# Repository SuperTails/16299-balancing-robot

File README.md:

# 16299 Balancing Robot PCB

Updated version of the PCB for 16299.

A submodule is used for some parts, so be sure to clone recursively:
```bash
git clone --recursive https://github.com/SuperTails/16299-balancing-robot.git
```

## Ordering PCBs

### 1 - Generate Bill of Materials

To generate the BoM:

1. Open the schematic editor
2. Open the "edit symbol fields" menu (table icon along the top ribbon)
3. Ensure the settings are as shown below
4. Hit "export".

### 2 - Generate Gerber Files

To generate the gerber files:
1. Open the PCB editor
2. File > Fabrication Outputs > Gerbers (.gbr)...
3. Ensure the settings are as shown below, including...
4. ... Make sure you set your output folder to `fab/`.
5. Click "Plot"

More information for plotting Gerber and Drill files is available on
[JLC's guide](https://jlcpcb.com/help/article/how-to-generate-gerber-and-drill-files-in-kicad-7).

### 3 - Generate Drill Files

To generate the drill files:
1. From the Gerbers menu in the previous step, click "Generate Drill Files"
3. Ensure the settings are as shown below
5. Click "Generate"

More information for plotting Gerber and Drill files is available on
[JLC's guide](https://jlcpcb.com/help/article/how-to-generate-gerber-and-drill-files-in-kicad-7).

### 4 - Generate Placement Files

To generate the placement files:
1. Open the PCB editor
2. File > Fabrication Outputs > Component Placement (.pos, .gbr)...
3. Ensure the settings are as shown below
4. Click "Generate Position File"

### 5 - File Format Conversion

To convert the files into JLC's preferred format, run the `format_bom.py` script:

```bash
python3 format_bom.py
```

This will generate `fab/bom-jlc.csv` and `fab/balancingrobot-top-pos-jlc.csv`,
which should be used for JLC's PCB assembly options (discussed later).

### 6 - Upload Gerbers

Zip the `fab/` directory and upload it to [JLC's website](https://jlcpcb.com/).
Rarely, the file upload can take up to 10 minutes to complete.

### 7 - Select Ordering Options

Most settings should default correctly,
but there are a few changes:

1. Set the quantity to the desired amount
2. Ensure that the order mark is set to "Order Number (Specify Position)"
3. Enable "PCB Assembly"
4. Hit "next"

### 8 - Uploading BOM and Placing Components

When prompted to "Upload BOM" and "Add CPL file",
upload `fab/bom-jlc.csv` and `fab/balancingrobot-top-pos-jlc.csv`.

It may issue a warning that D9 and D10 are not present in the CPL,
this is normal and you can continue.
D9 and D10 are the IR LEDs which are mounted on the underside of the board,
and doing assembly for both top and bottom components makes shipping difficult.

All parts should be selected in the right column and there should be no other errors.

When moving on to placement, JLC may note that
"The system detects component that may be offset from the PCB,
does it try to automatically align it?"
Click **cancel** on this prompt, as it will displace many of the components to the wrong place.

The through-hole components typically need to be both rotated and dragged to fit;
the surface mount components should **only be rotated**.

Ensure that all surface mount components
**have the pink dot (pin 1) aligned with the corresponding silkscreen arrow**.
Some of the SMD components may be upside-down.

There will be four rows of header pins far above the rest of the PCB (shown below);
these are the sockets for the Arduino Nano and the motor driver.
Be sure to place them as well.

Once placement is finished, the board should appear as shown below:

When prompted to select a category for your order, I usually select "Robot",
as shown below:

This completes all the placement steps,
simply complete the rest of the checkout steps to order the PCB.

**After ordering, you may receive an email saying that the footprint of the 7-segment display is incorrect.**
**As long as the decimal point is on the bottom and the pink dot is in the bottom left, reply to the email and say the placement is correct.**

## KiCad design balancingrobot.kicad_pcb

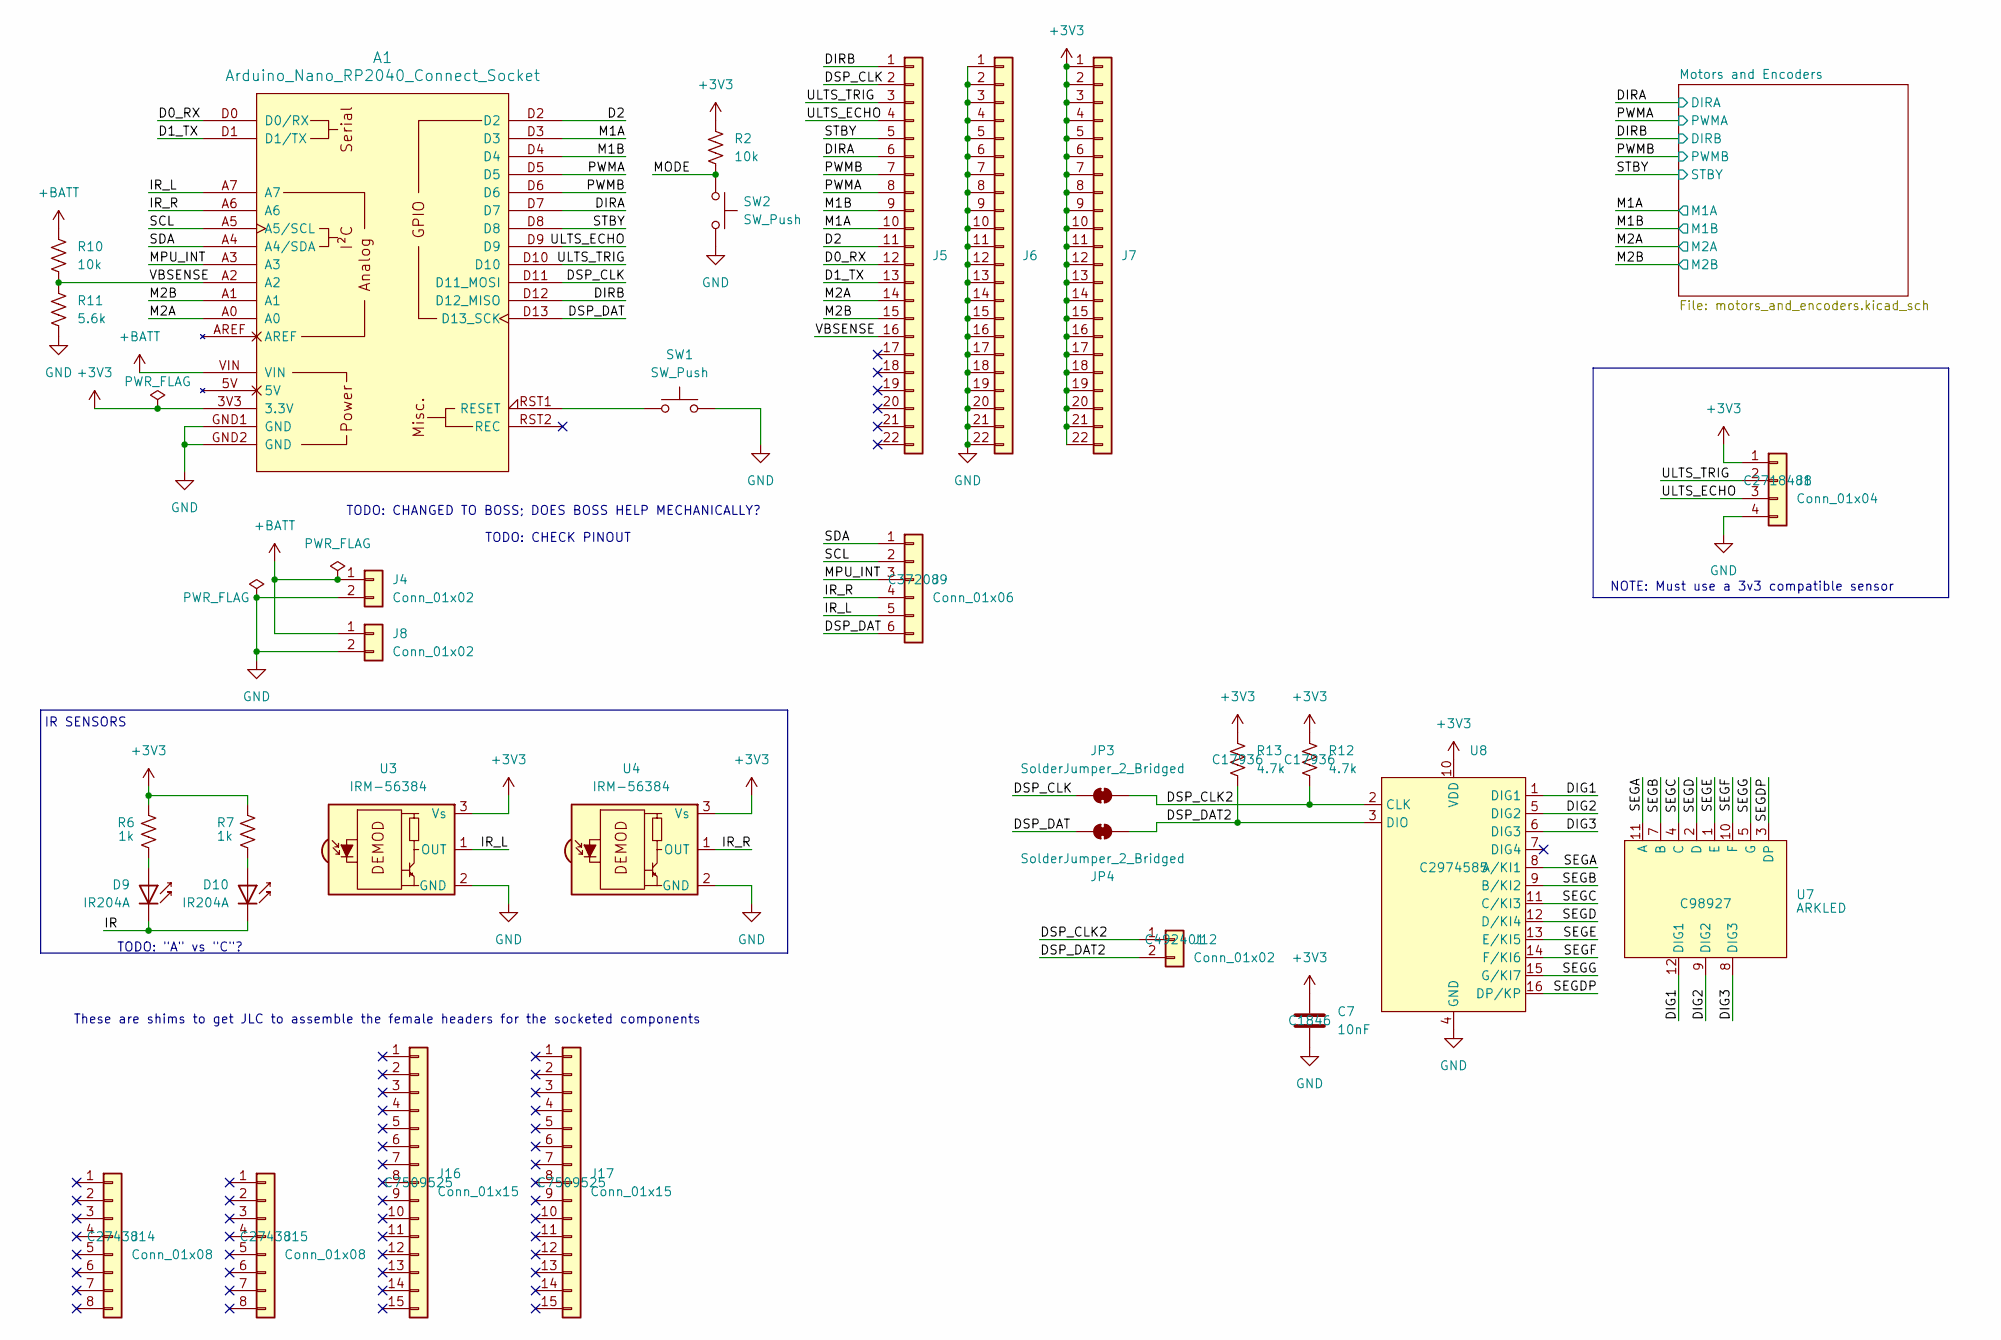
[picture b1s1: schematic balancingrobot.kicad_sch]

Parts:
A1: Arduino_Nano_RP2040_Connect_Socket; Arduino_Nano_Every_Socket
C7: 10nF; C_1206_3216Metric; JLC P/N C1846
D9, D10: IR204A; LED_D3.0mm_IRBlack; JLC P/N C2936547
J1: Conn_01x04; PinSocket_1x04_P2.54mm_Vertical; JLC P/N C2718488
J4: Conn_01x02; JST_XH_S2B-XH-A-1_1x02_P2.50mm_Horizontal; JLC P/N C163035
J5, J6, J7: Conn_01x22; PinHeader_1x22_P2.54mm_Vertical; JLC P/N C725954
J8, J12: Conn_01x02; PinHeader_1x02_P2.54mm_Vertical; JLC P/N C492401
J9: Conn_01x06; PinHeader_1x06_P2.54mm_Vertical; JLC P/N C37208
J14, J15: Conn_01x08; PinSocket_1x08_P2.54mm_Vertical; JLC P/N C27438
J16, J17: Conn_01x15; PinSocket_1x15_P2.54mm_Vertical; JLC P/N C7509525
JP3, JP4: SolderJumper_2_Bridged; SolderJumper-2_P1.3mm_Bridged_RoundedPad1.0x1.5mm
R2, R10: 10k; R_1206_3216Metric; JLC P/N C17902
R6, R7: 1k; R_1206_3216Metric; JLC P/N C4410
R11: 5.6k; R_1206_3216Metric; JLC P/N C18028
R12, R13: 4.7k; R_1206_3216Metric; JLC P/N C17936
SW1, SW2: SW_Push; SW_PUSH_6mm; JLC P/N C255811
U3, U4: IRM-56384; Vishay_MOLD-3Pin; JLC P/N C72048
U7: ARKLED; ARKLED(Wuxi ARK Tech Elec) SP420361N; JLC P/N C98927
U8: SOP-16_3.9x9.9mm_P1.27mm; JLC P/N C2974585

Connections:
+3V3: A1.3V3 (3.3V), C7.1, J1.1, J7.1, J7.2, J7.3, J7.4, J7.5, J7.6, J7.7, J7.8, J7.9, J7.10, J7.11, J7.12, J7.13, J7.14, J7.15, J7.16, J7.17, J7.18, J7.19, J7.20, J7.21, J7.22, R2.1, R6.2, R7.1, R12.1, R13.1, U3.3 (Vs), U4.3 (Vs), U8.10 (VDD); also elsewhere on the board
+BATT: A1.VIN, J4.1, J8.1, R10.1; also elsewhere on the board
/D0_RX: A1.D0 (D0/RX), J5.12
/D1_TX: A1.D1 (D1/TX), J5.13
/D2: A1.D2, J5.11
/DIG1: U7.12 (DIG1), U8.1 (DIG1)
/DIG2: U7.9 (DIG2), U8.5 (DIG2)
/DIG3: U7.8 (DIG3), U8.6 (DIG3)
/DIRA: A1.D7, J5.6; also elsewhere on the board
/DIRB: A1.D12 (D12_MISO), J5.1; also elsewhere on the board
/DSP_CLK: A1.D11 (D11_MOSI), J5.2, JP3.1 (A)
/DSP_CLK2: J12.1, JP3.2 (B), R12.2, U8.2 (CLK)
/DSP_DAT: A1.D13 (D13_SCK), J9.6, JP4.1 (A)
/DSP_DAT2: J12.2, JP4.2 (B), R13.2, U8.3 (DIO)
/IR: D9.1 (K), D10.1 (K)
/IR_L: A1.A7, J9.5, U3.1 (OUT)
/IR_R: A1.A6, J9.4, U4.1 (OUT)
/M1A: A1.D3, J5.10; also elsewhere on the board
/M1B: A1.D4, J5.9; also elsewhere on the board
/M2A: A1.A0, J5.14; also elsewhere on the board
/M2B: A1.A1, J5.15; also elsewhere on the board
/MODE: R2.2, SW2.1
/MPU_INT: A1.A3, J9.3
/PWMA: A1.D5, J5.8; also elsewhere on the board
/PWMB: A1.D6, J5.7; also elsewhere on the board
/SCL: A1.A5 (A5/SCL), J9.2
/SDA: A1.A4 (A4/SDA), J9.1
/SEGA: U7.11 (A), U8.8 (A/KI1)
/SEGB: U7.7 (B), U8.9 (B/KI2)
/SEGC: U7.4 (C), U8.11 (C/KI3)
/SEGD: U7.2 (D), U8.12 (D/KI4)
/SEGDP: U7.3 (DP), U8.16 (DP/KP)
/SEGE: U7.1 (E), U8.13 (E/KI5)
/SEGF: U7.10 (F), U8.14 (F/KI6)
/SEGG: U7.5 (G), U8.15 (G/KI7)
/STBY: A1.D8, J5.5; also elsewhere on the board
/ULTS_ECHO: A1.D9, J1.3, J5.4
/ULTS_TRIG: A1.D10, J1.2, J5.3
/VBSENSE: A1.A2, J5.16, R10.2, R11.1
GND: A1.GND1 (GND), A1.GND2 (GND), C7.2, J1.4, J4.2, J6.1, J6.2, J6.3, J6.4, J6.5, J6.6, J6.7, J6.8, J6.9, J6.10, J6.11, J6.12, J6.13, J6.14, J6.15, J6.16, J6.17, J6.18, J6.19, J6.20, J6.21, J6.22, J8.2, R11.2, SW1.2, SW2.2, U3.2 (GND), U4.2 (GND), U8.4 (GND); also elsewhere on the board
unnamed: A1.RST1 (RESET), SW1.1
unnamed: D9.2 (A), R6.1
unnamed: D10.2 (A), R7.2

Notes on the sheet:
IR SENSORS
TODO: "A" vs "C"?
These are shims to get JLC to assemble the female headers for the socketed components
NOTE: Must use a 3v3 compatible sensor
TODO: CHECK PINOUT
TODO: CHANGED TO BOSS; DOES BOSS HELP MECHANICALLY?

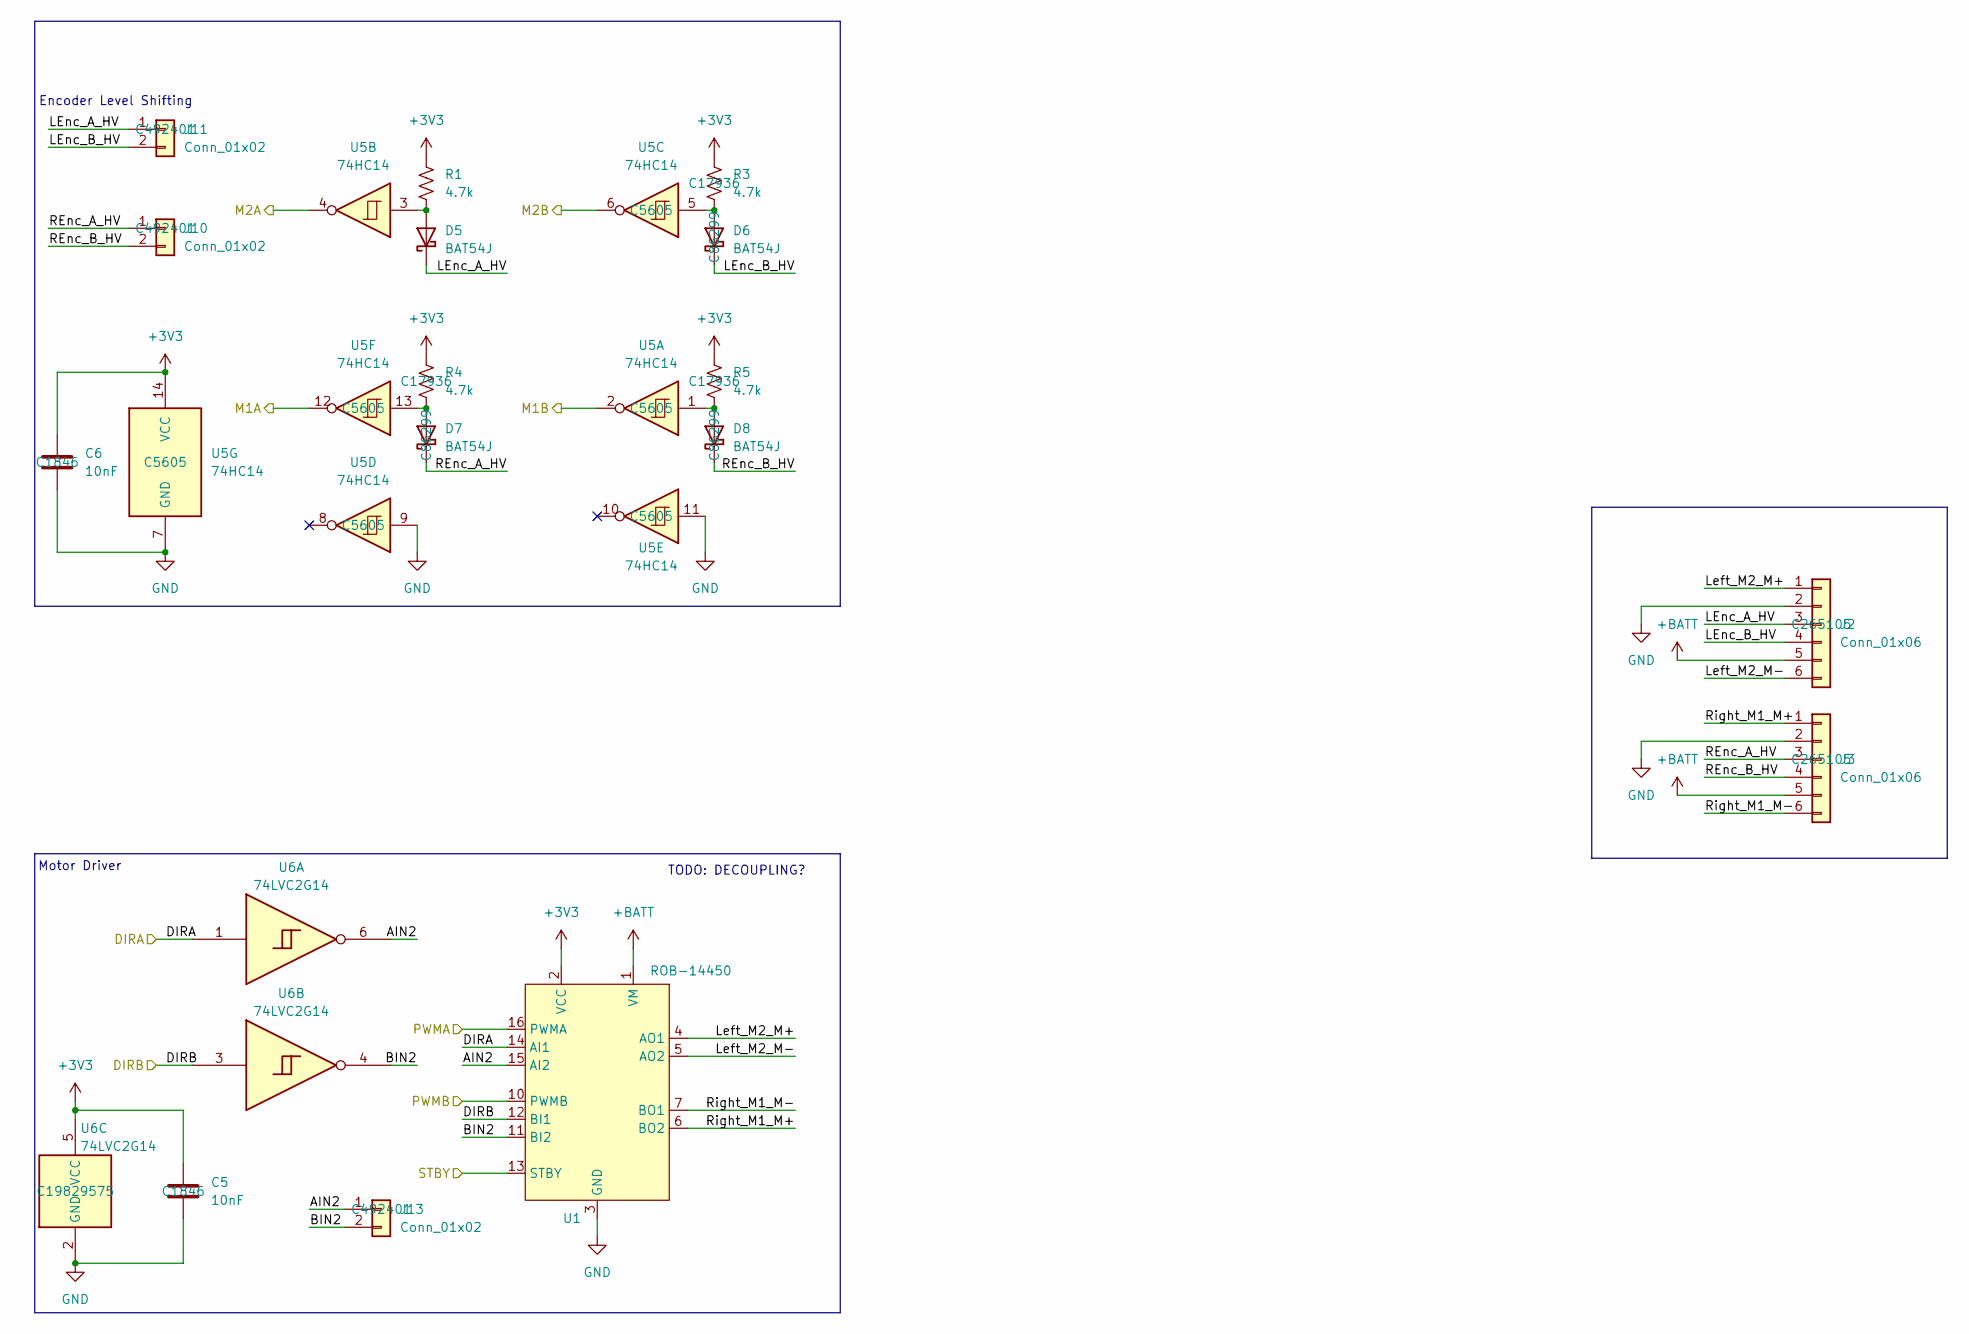
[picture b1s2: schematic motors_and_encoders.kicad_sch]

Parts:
C5, C6: 10nF; C_1206_3216Metric; JLC P/N C1846
D5, D6, D7, D8: BAT54J; D_SOD-323F; JLC P/N C86299
J2, J3: Conn_01x06; JST_PH_S6B-PH-K_1x06_P2.00mm_Horizontal; JLC P/N C265105
J10, J11, J13: Conn_01x02; PinHeader_1x02_P2.54mm_Vertical; JLC P/N C492401
R1, R3, R4, R5: 4.7k; R_1206_3216Metric; JLC P/N C17936
U1: ROB-14450; ROB-14451
U5: 74HC14; SOIC-14_3.9x8.7mm_P1.27mm; JLC P/N C5605
U6: 74LVC2G14; SOT-363_SC-70-6; JLC P/N C19829575

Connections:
+3V3: C5.1, C6.1, R1.2, R3.2, R4.2, R5.2, U1.2 (VCC), U5.14 (VCC), U6.5 (VCC); also elsewhere on the board
+BATT: J2.5, J3.5, U1.1 (VM); also elsewhere on the board
/DIRA: U1.14 (AI1), U6.1; also elsewhere on the board
/DIRB: U1.12 (BI1), U6.3; also elsewhere on the board
/M1A: U5.12; also elsewhere on the board
/M1B: U5.2; also elsewhere on the board
/M2A: U5.4; also elsewhere on the board
/M2B: U5.6; also elsewhere on the board
/Motors and Encoders/AIN2: J13.1, U1.15 (AI2), U6.6
/Motors and Encoders/BIN2: J13.2, U1.11 (BI2), U6.4
/Motors and Encoders/LEnc_A_HV: D5.1 (K), J2.3, J11.1
/Motors and Encoders/LEnc_B_HV: D6.1 (K), J2.4, J11.2
/Motors and Encoders/Left_M2_M+: J2.1, U1.4 (AO1)
/Motors and Encoders/Left_M2_M-: J2.6, U1.5 (AO2)
/Motors and Encoders/REnc_A_HV: D7.1 (K), J3.3, J10.1
/Motors and Encoders/REnc_B_HV: D8.1 (K), J3.4, J10.2
/Motors and Encoders/Right_M1_M+: J3.1, U1.6 (BO2)
/Motors and Encoders/Right_M1_M-: J3.6, U1.7 (BO1)
/PWMA: U1.16 (PWMA); also elsewhere on the board
/PWMB: U1.10 (PWMB); also elsewhere on the board
/STBY: U1.13 (STBY); also elsewhere on the board
GND: C5.2, C6.2, J2.2, J3.2, U1.3 (GND), U1.8 (GND), U1.9 (GND), U5.7 (GND), U5.9, U5.11, U6.2 (GND); also elsewhere on the board
unnamed: D5.2 (A), R1.1, U5.3
unnamed: D6.2 (A), R3.1, U5.5
unnamed: D7.2 (A), R4.1, U5.13
unnamed: D8.2 (A), R5.1, U5.1

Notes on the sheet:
Encoder Level Shifting
TODO: DECOUPLING?
Motor Driver

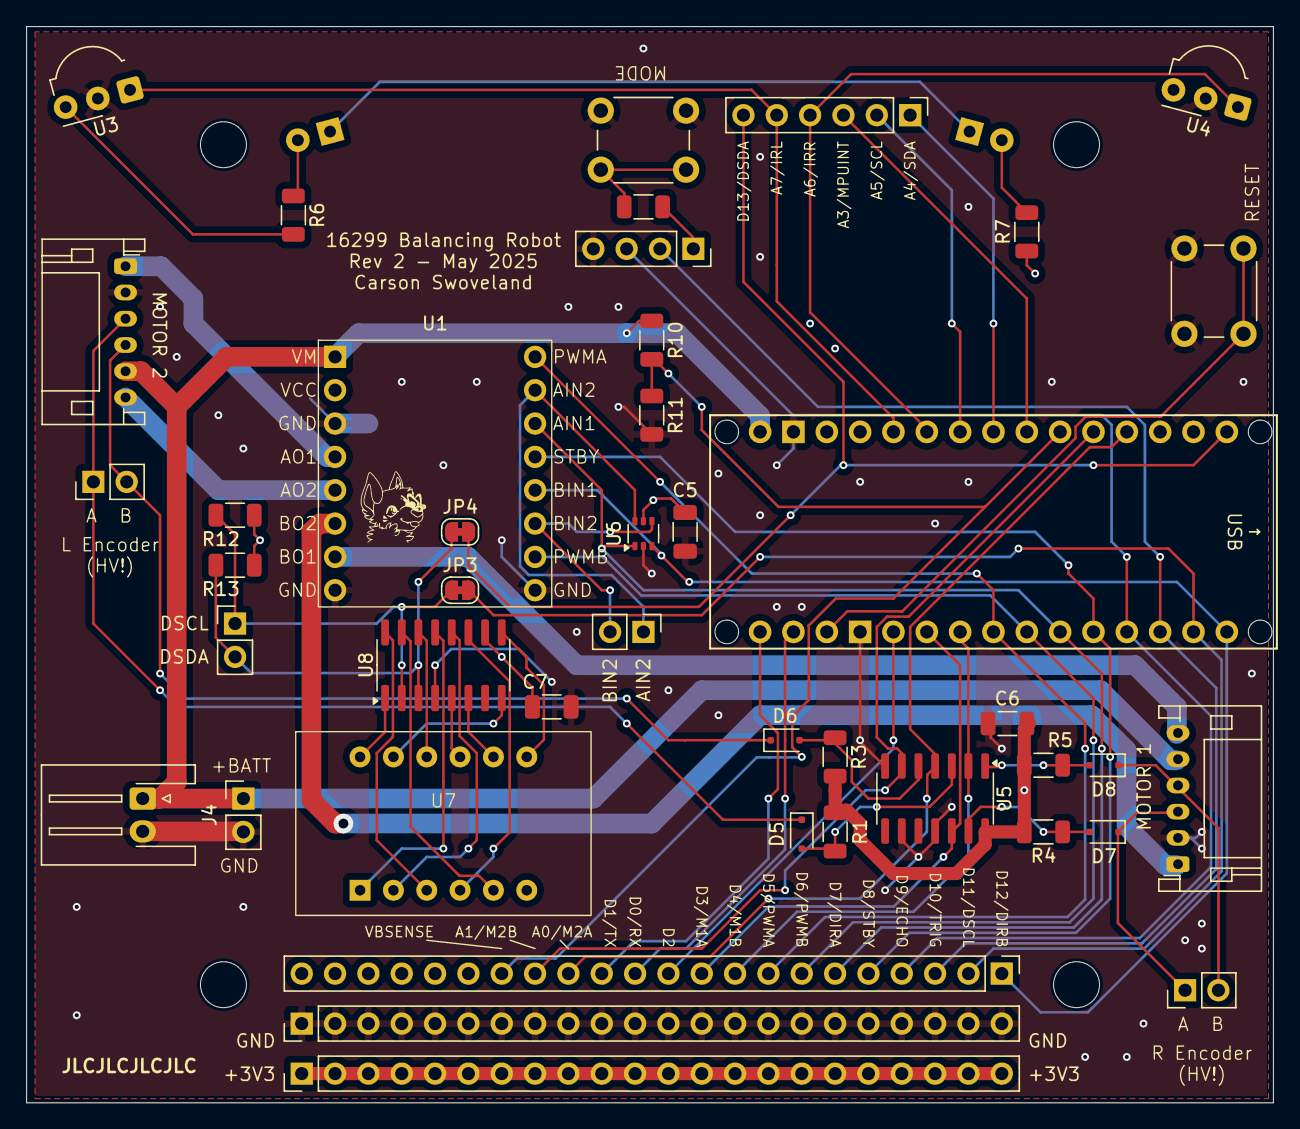
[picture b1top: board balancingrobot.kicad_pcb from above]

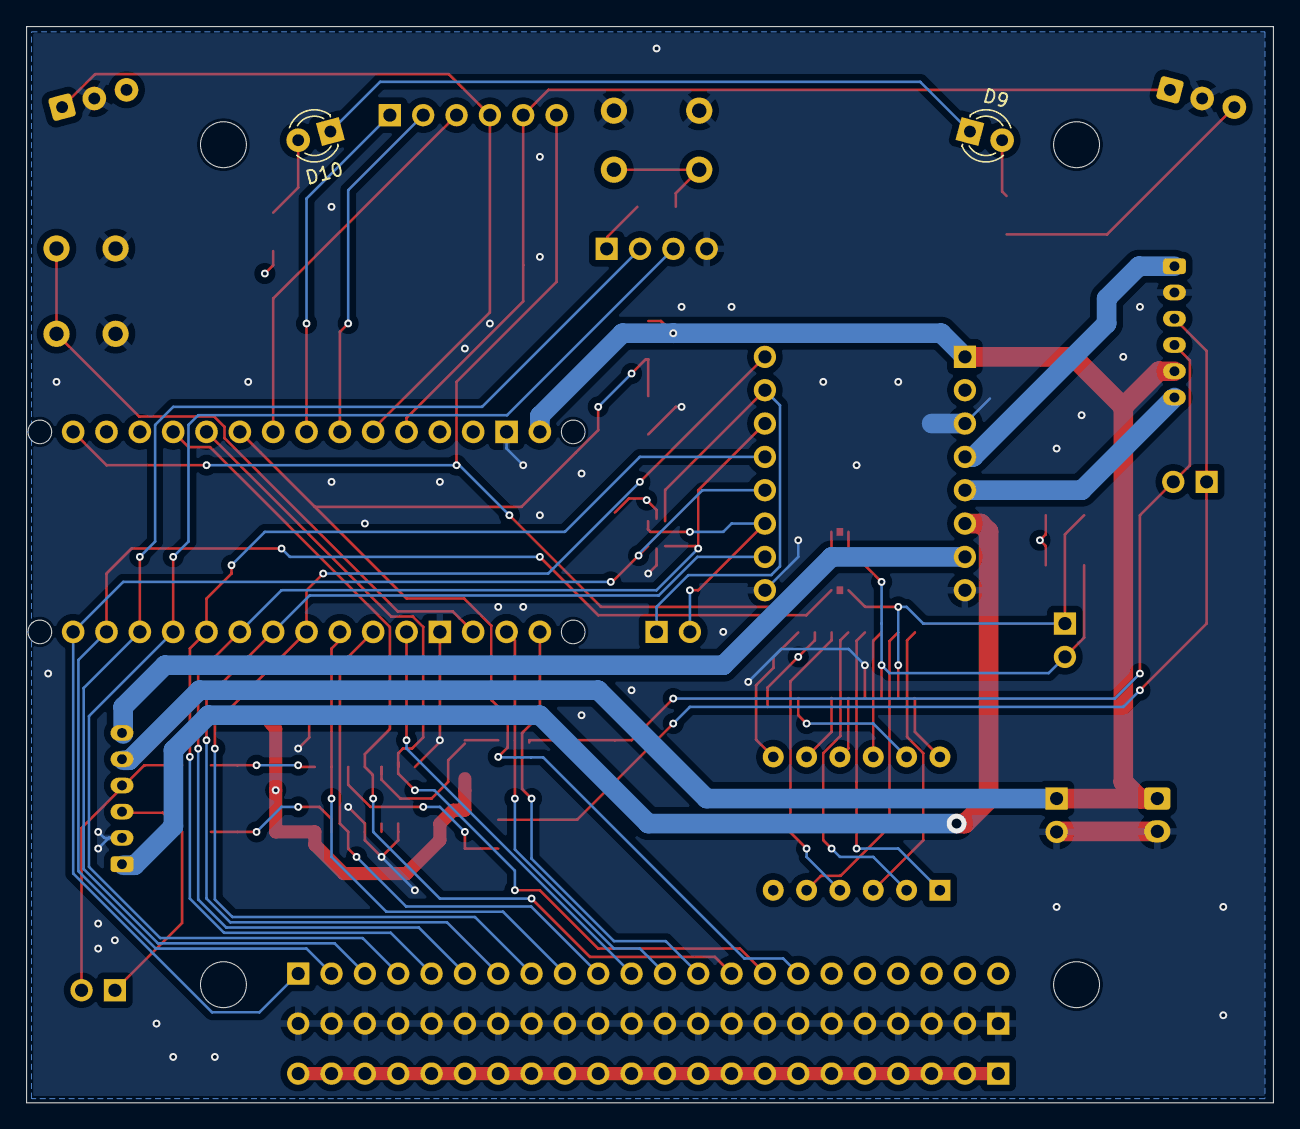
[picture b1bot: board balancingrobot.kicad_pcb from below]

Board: 4 copper layers, 95.0 x 82.0 mm, 45 parts (2 on the bottom side), 57 nets.

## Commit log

2025-03-24 Update silkscreen and change to 4 layer
2025-03-26 Remove MPU6050
